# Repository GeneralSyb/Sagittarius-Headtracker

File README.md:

These are the project files for the Sagittarius wireless headtracker.

A bit of background:
This project started off as a way to find a cheap high performance headtracker, but it didn't take me long to find out that a cheap and simple wireless headtracker would be more suited for my needs.
I started off with some cheap IMU modules and an ESP32, however most of these sensors were fakes because the real ones weren't in production anymore. They worked, but they had issues with drift and low dynamic accuracy.
The first prototype that actually worked well used a BNO085 sensor breakout board from Adafruit and an ESP32-S2 Wemos board to process and transmit the data over WiFi to Opentrack that was using the UDP input.

Do not that everything you will find here is not a complete and ready to go device you can just build. Knowledge about electronics, embedded software and hardware design is REQUIRED to get anything out of this. After all, this more of a dump of my knowledge, findings and what I've made than a complete project.
The following thins might be of interest if you are looking to make something like this:
- PCB Schematics
- Sagittarius S1 Firmware
  - Data transmit function (packet construction)
  - Quaternion processing

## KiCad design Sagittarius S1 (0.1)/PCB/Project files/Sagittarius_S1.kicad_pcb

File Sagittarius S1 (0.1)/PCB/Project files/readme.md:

Please refer to the PCB schematic PDF to get any sort of information about the S1 V0.1 prototype. The PCB design is flawed and rushed, isn't even complete and shouldn't be considered as something that you should make.

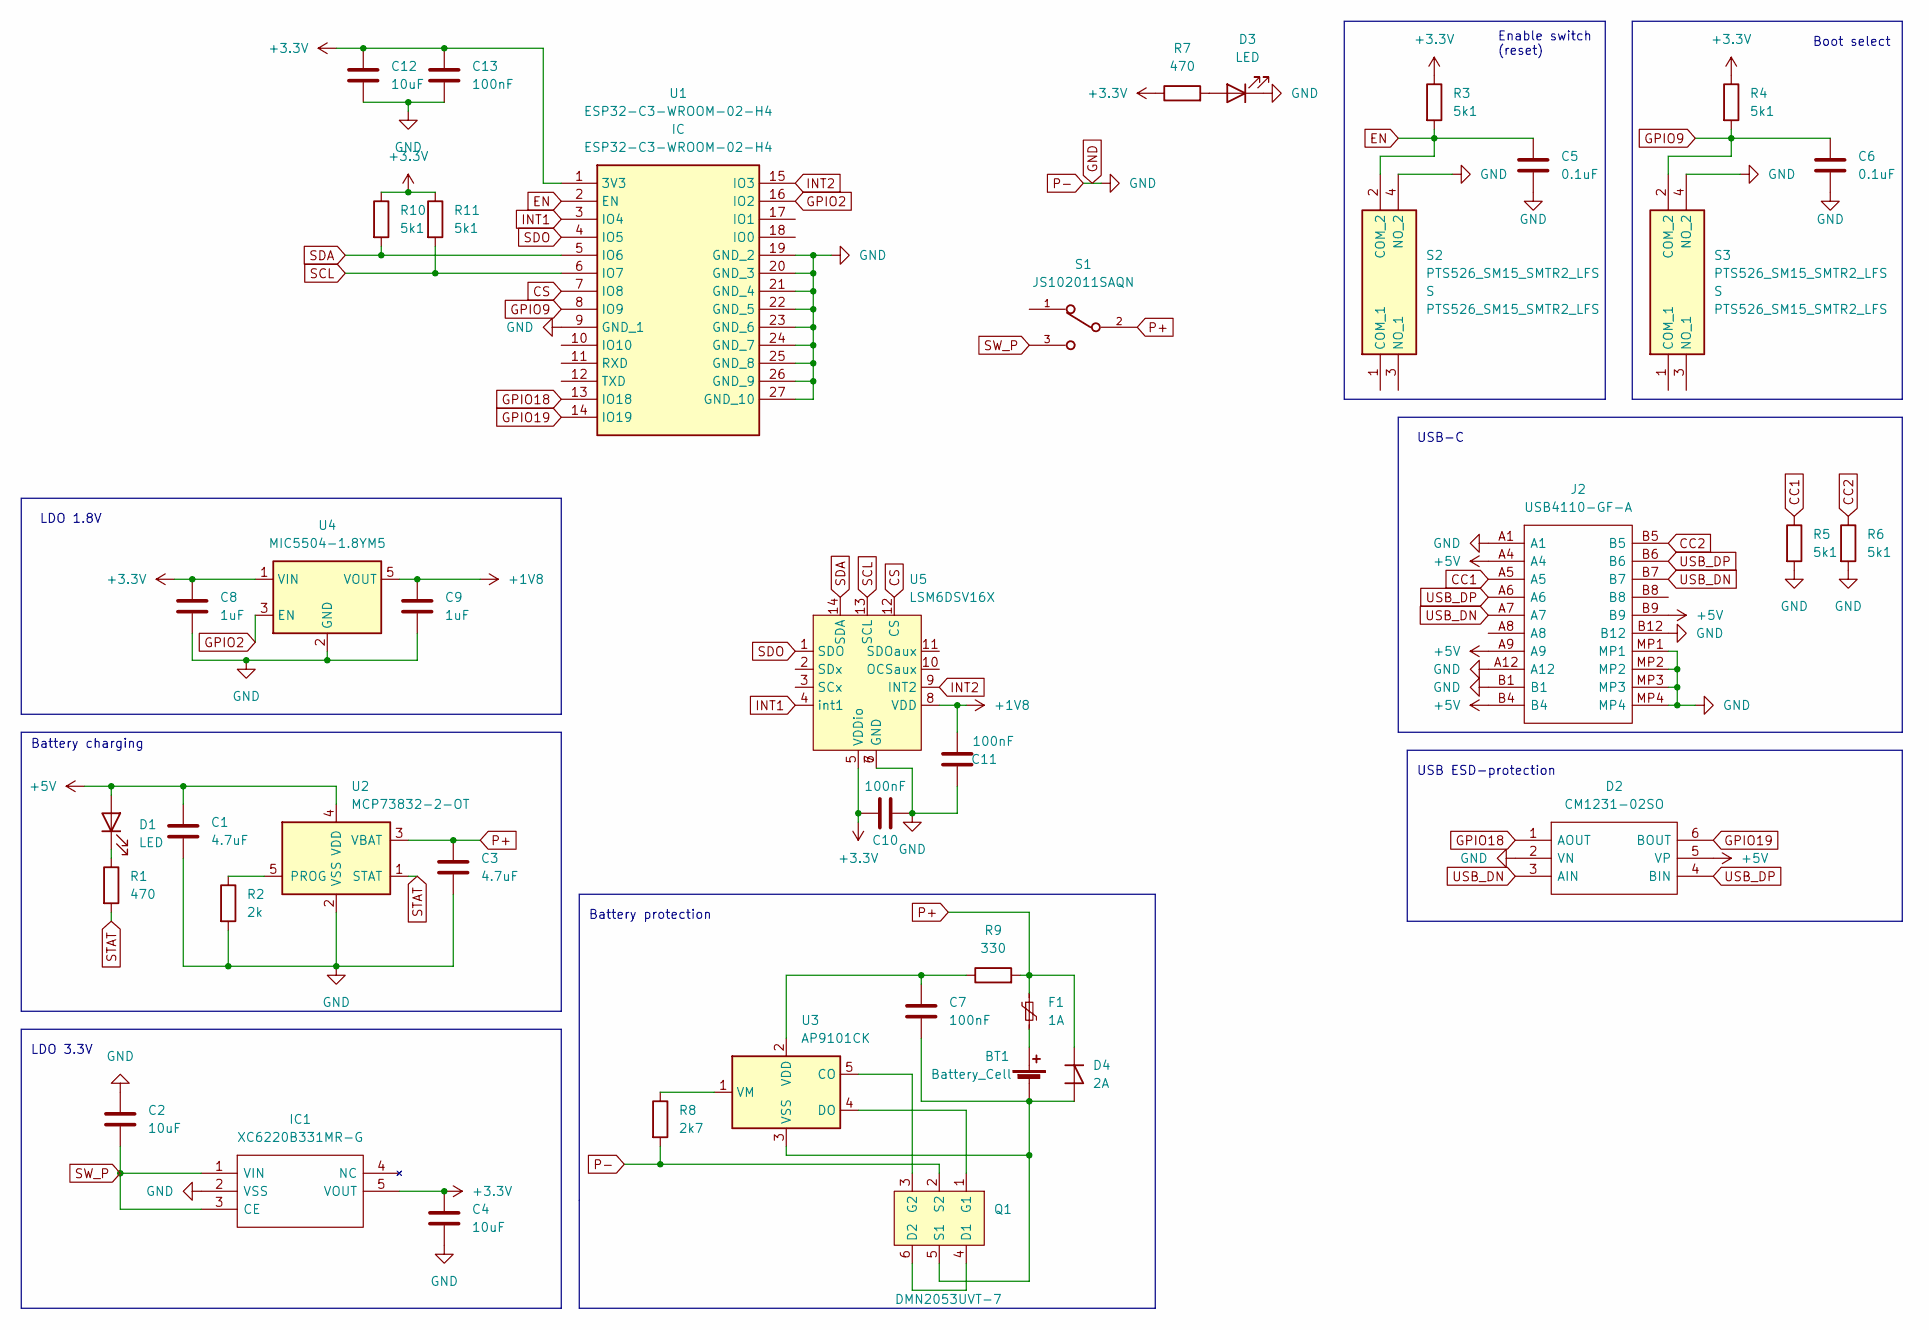
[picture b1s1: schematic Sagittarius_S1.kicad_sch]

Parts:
BT1: Battery_Cell; BatteryHolder_Keystone_1042_1x18650
C1, C3: 4.7uF; C_0402_1005Metric
C2, C4, C12: 10uF; C_0402_1005Metric
C5, C6: 0.1uF; C_0402_1005Metric
C7, C10, C11, C13: 100nF; C_0402_1005Metric
C8, C9: 1uF; C_0402_1005Metric
D1, D3: LED; LED_0603_1608Metric
D2: CM1231-02SO; SOT95P280X145-6N; Mouser Part Number 748-CM1231-02SO
D4: 2A; D_SOD-123F
F1: 1A; Fuse_1812_4532Metric_Pad1.30x3.40mm_HandSolder
IC1: XC6220B331MR-G; SOT95P280X130-5N; Mouser Part Number 865-XC6220B331MR-G
J2: USB4110-GF-A; USB4110GFA; Mouser Part Number 640-USB4110-GF-A
Q1: DMN2053UVT-7; SOT-23-6
R1, R7: 470; R_0402_1005Metric
R2: 2k; R_0402_1005Metric
R3, R4, R5, R6, R10, R11: 5k1; R_0402_1005Metric
R8: 2k7; R_0402_1005Metric
R9: 330; R_0402_1005Metric
S1: JS102011SAQN; SW_JS102011SAQN
S2, S3: PTS526_SM15_SMTR2_LFS; PTS526SM15SMTR2LFS; Mouser Part Number 611-PTS526SM15SMTR2L
U1: ESP32-C3-WROOM-02-H4; ESP32C3WROOM02H4; Mouser Part Number 356-ESP32C3WROOM02H4
U2: MCP73832-2-OT; SOT-23-5
U3: AP9101CK; SOT-23-5
U4: MIC5504-1.8YM5; SOT-23-5
U5: LSM6DSV16X; LGA-14L 2.5 x 3.0

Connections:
+1V8: C9.1, C11.1, U4.5 (VOUT), U5.8 (VDD)
+3.3V: C4.1, C8.1, C10.2, C12.1, C13.1, IC1.5 (VOUT), R3.1, R4.1, R7.1, R10.1, R11.1, U1.1 (3V3), U4.1 (VIN), U5.5 (VDDio)
+5V: C1.2, D1.2 (A), D2.5 (VP), J2.A4, J2.A9, J2.B4, J2.B9, U2.4 (VDD)
CC1: J2.A5, R5.1
CC2: J2.B5, R6.1
CS: U1.7 (IO8), U5.12 (CS)
EN: C5.1, R3.2, S2.2 (COM_2), U1.2 (EN)
GND: C1.1, C2.1, C3.1, C4.2, C5.2, C6.2, C8.2, C9.2, C10.1, C11.2, C12.2, C13.2, D2.2 (VN), D3.1 (K), IC1.2 (VSS), J2.A1, J2.A12, J2.B1, J2.B12, J2.MP1, J2.MP2, J2.MP3, J2.MP4, Q1.2 (S2), R2.2, R5.2, R6.2, R8.2, S2.4 (NO_2), S3.4 (NO_2), U1.9 (GND_1), U1.19 (GND_2), U1.20 (GND_3), U1.21 (GND_4), U1.22 (GND_5), U1.23 (GND_6), U1.24 (GND_7), U1.25 (GND_8), U1.26 (GND_9), U1.27 (GND_10), U2.2 (VSS), U4.2 (GND), U5.6 (GND), U5.7 (GND)
GPIO2: U1.16 (IO2), U4.3 (EN)
GPIO9: C6.1, R4.2, S3.2 (COM_2), U1.8 (IO9)
GPIO18: D2.1 (AOUT), U1.13 (IO18)
GPIO19: D2.6 (BOUT), U1.14 (IO19)
INT1: U1.3 (IO4), U5.4 (int1)
INT2: U1.15 (IO3), U5.9 (INT2)
unnamed: BT1.1 (+), F1.2
unnamed: BT1.2 (-), C7.2, D4.2 (A), Q1.5 (S1), U3.3 (VSS)
unnamed: C7.1, R9.1, U3.2 (VDD)
unnamed: D1.1 (K), R1.1
unnamed: D3.2 (A), R7.2
unnamed: Q1.1 (G1), U3.4 (DO)
unnamed: Q1.3 (G2), U3.5 (CO)
unnamed: Q1.4 (D1), Q1.6 (D2)
unnamed: R2.1, U2.5 (PROG)
unnamed: R8.1, U3.1 (VM)
P+: C3.2, D4.1 (K), F1.1, R9.2, S1.2, U2.3 (VBAT)
SCL: R11.2, U1.6 (IO7), U5.13 (SCL)
SDA: R10.2, U1.5 (IO6), U5.14 (SDA)
SDO: U1.4 (IO5), U5.1 (SDO)
STAT: R1.2, U2.1 (STAT)
SW_P: C2.2, IC1.1 (VIN), IC1.3 (CE), S1.3
USB_DN: D2.3 (AIN), J2.A7, J2.B7
USB_DP: D2.4 (BIN), J2.A6, J2.B6

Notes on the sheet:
Boot select
Battery protection
LDO 1.8V
USB-C
Battery charging
LDO 3.3V
Enable switch (reset)
USB ESD-protection

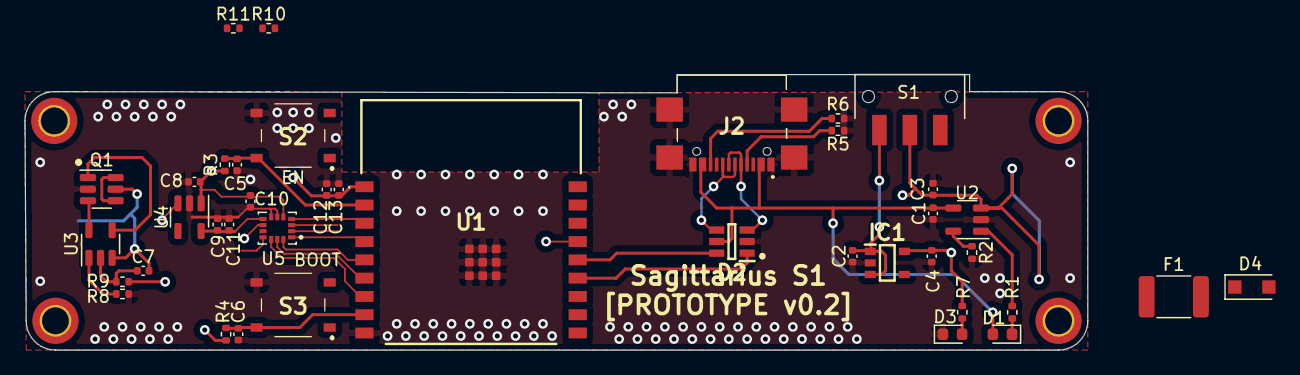
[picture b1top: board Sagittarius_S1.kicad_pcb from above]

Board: 4 copper layers, 87.2 x 22.6 mm, 41 parts (1 on the bottom side), 32 nets.

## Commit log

2024-01-27 Sagittarius S1 (V0.1) upload
